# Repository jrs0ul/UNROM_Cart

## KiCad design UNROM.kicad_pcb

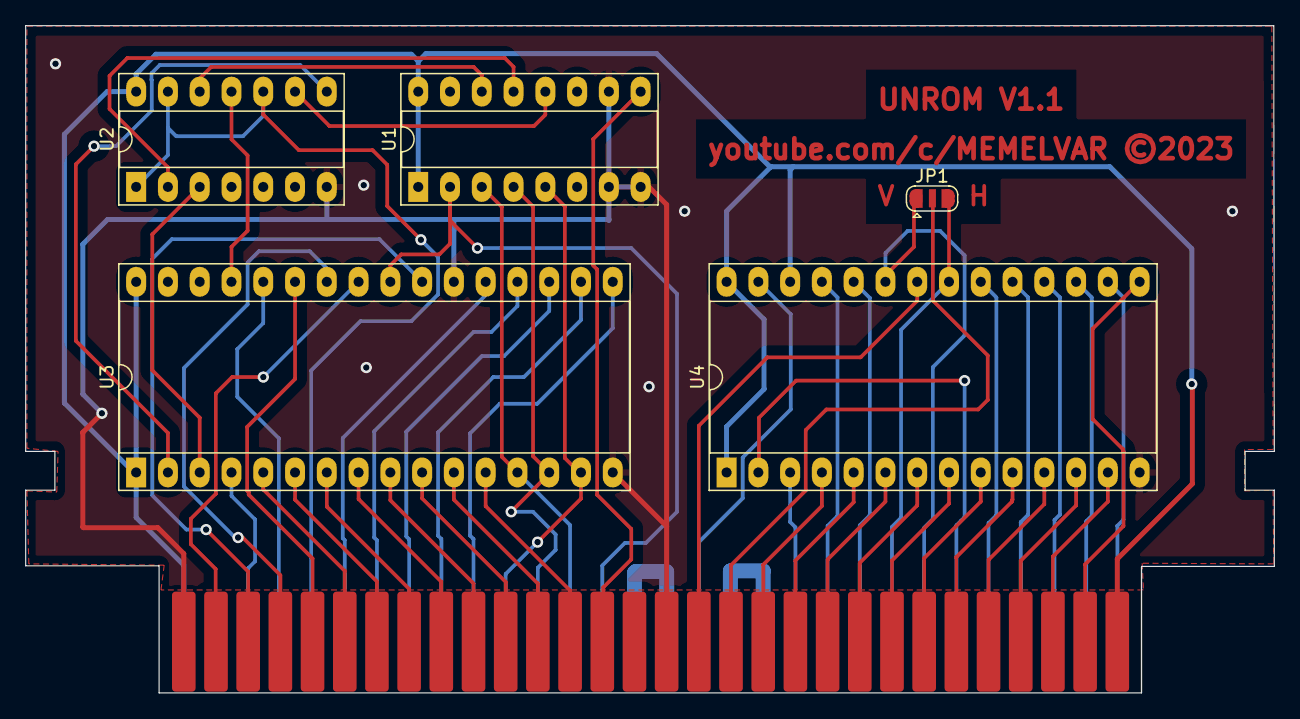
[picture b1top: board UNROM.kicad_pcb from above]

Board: 2 copper layers, 99.8 x 53.3 mm, 6 parts (0 on the bottom side), 60 nets.

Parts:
JP1: SolderJumper_3_Open; SolderJumper-3_P1.3mm_Open_RoundedPad1.0x1.5mm
U1: 74LS161; DIP-16_W7.62mm_Socket_LongPads
U2: 74LS32; DIP-14_W7.62mm_Socket_LongPads
U3: W27E010-70; DIP-32_W15.24mm_Socket_LongPads
U4: CXK5864BP-10L; DIP-28_W15.24mm_Socket_LongPads
U5: Famicom_Cart_Port; Famicom_connector

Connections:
+5V: U1.1 (~MR), U1.16 (VCC), U2.14 (VCC), U3.1 (VPP), U3.32 (VCC), U4.1 (NC), U4.26 (CE2), U4.28 (VCC), U5.30 (+5V), U5.31 (+5V)
/CPU_A0: U3.12 (A0), U5.13 (CPU_A0)
/CPU_A1: U3.11 (A1), U5.12 (CPU_A1)
/CPU_A2: U3.10 (A2), U5.11 (CPU_A2)
/CPU_A3: U3.9 (A3), U5.10 (CPU_A3)
/CPU_A4: U3.8 (A4), U5.9
/CPU_A5: U3.7 (A5), U5.8
/CPU_A6: U3.6 (A6), U5.7
/CPU_A7: U3.5 (A7), U5.6
/CPU_A8: U3.27 (A8), U5.5
/CPU_A9: U3.26 (A9), U5.4
/CPU_A10: U3.23 (A10), U5.3
/CPU_A11: U3.25 (A11), U5.2
/CPU_A12: U3.4 (A12), U5.33 (CPU_A12)
/CPU_A13: U3.28 (A13), U5.34 (CPU_A13)
/CPU_D0: U1.3 (D0), U3.13 (D0), U5.43 (CPU_D0)
/CPU_D1: U1.4 (D1), U3.14 (D1), U5.42 (CPU_D1)
/CPU_D2: U1.5 (D2), U3.15 (D2), U5.41 (CPU_D2)
/CPU_D3: U3.17 (D3), U5.40 (CPU_D3)
/CPU_D4: U3.18 (D4), U5.39 (CPU_D4)
/CPU_D5: U3.19 (D5), U5.38 (CPU_D5)
/CPU_D6: U3.20 (D6), U5.37 (CPU_D6)
/CPU_D7: U3.21 (D7), U5.36 (CPU_D7)
/PPU_A0: U4.10 (A0), U5.25 (PPU_A0)
/PPU_A1: U4.9 (A1), U5.24 (PPU_A1)
/PPU_A2: U4.8 (A2), U5.23 (PPU_A2)
/PPU_A3: U4.7 (A3), U5.22 (PPU_A3)
/PPU_A4: U4.6 (A4), U5.21 (PPU_A4)
/PPU_A5: U4.5 (A5), U5.20 (PPU_A5)
/PPU_A6: U4.4 (A6), U5.19 (PPU_A6)
/PPU_A7: U4.3 (A7), U5.50 (PPU_A7)
/PPU_A8: U4.25 (A8), U5.51 (PPU_A8)
/PPU_A9: U4.24 (A9), U5.52 (PPU_A9)
/PPU_A10: JP1.3 (B), U4.21 (A10), U5.53 (PPU_A10)
/PPU_A11: JP1.1 (A), U4.23 (A11), U5.54 (PPU_A11)
/PPU_A12: U4.2 (A12), U5.55 (PPU_A12)
/PPU_D0: U4.11 (D0), U5.26 (PPU_D0)
/PPU_D1: U4.12 (D1), U5.27 (PPU_D1)
/PPU_D2: U4.13 (D2), U5.28 (PPU_D2)
/PPU_D3: U4.15 (D3), U5.29 (PPU_D3)
/PPU_D4: U4.16 (D4), U5.60 (PPU_D4)
/PPU_D5: U4.17 (D5), U5.59 (PPU_D5)
/PPU_D6: U4.18 (D6), U5.58 (PPU_D6)
/PPU_D7: U4.19 (D7), U5.57 (PPU_D7)
GND: U1.7 (CEP), U1.8 (GND), U1.10 (CET), U2.7 (GND), U3.16 (GND), U3.22 (/CE), U4.14 (GND), U5.1, U5.16 (GND)
unnamed: JP1.2 (C), U5.18 (CIRAM_A10)
unnamed: U1.2 (CP), U3.24 (/OE), U5.44 (/ROMSEL)
unnamed: U1.9 (~PE), U5.14 (CPU_R/W)
unnamed: U1.12 (Q2), U2.9
unnamed: U1.13 (Q1), U2.2
unnamed: U1.14 (Q0), U2.12
unnamed: U2.1, U2.10, U2.13, U5.35 (CPU_A14)
unnamed: U2.3, U3.3 (A15)
unnamed: U2.8, U3.2 (A16)
unnamed: U2.11, U3.29 (A14)
unnamed: U4.20 (/CE1), U5.56 (PPU_A13)
unnamed: U4.22 (/OE), U5.17 (PPU_/RD)
unnamed: U4.27 (/WE), U5.47 (PPU_/WR)
unnamed: U5.45 (AUDIO_IN), U5.46 (AUDIO_OUT)
unnamed: U5.48 (CIRAM_/CE), U5.49 (PPU_/A13)

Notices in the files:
UNROM.kicad_pcb:
youtube.com/c/MEMELVAR ©2023
